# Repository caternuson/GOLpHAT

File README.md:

# GOLpHAT
Eagle PCB files for Raspberry Pi Game Of Life psuedo-HAT interface.

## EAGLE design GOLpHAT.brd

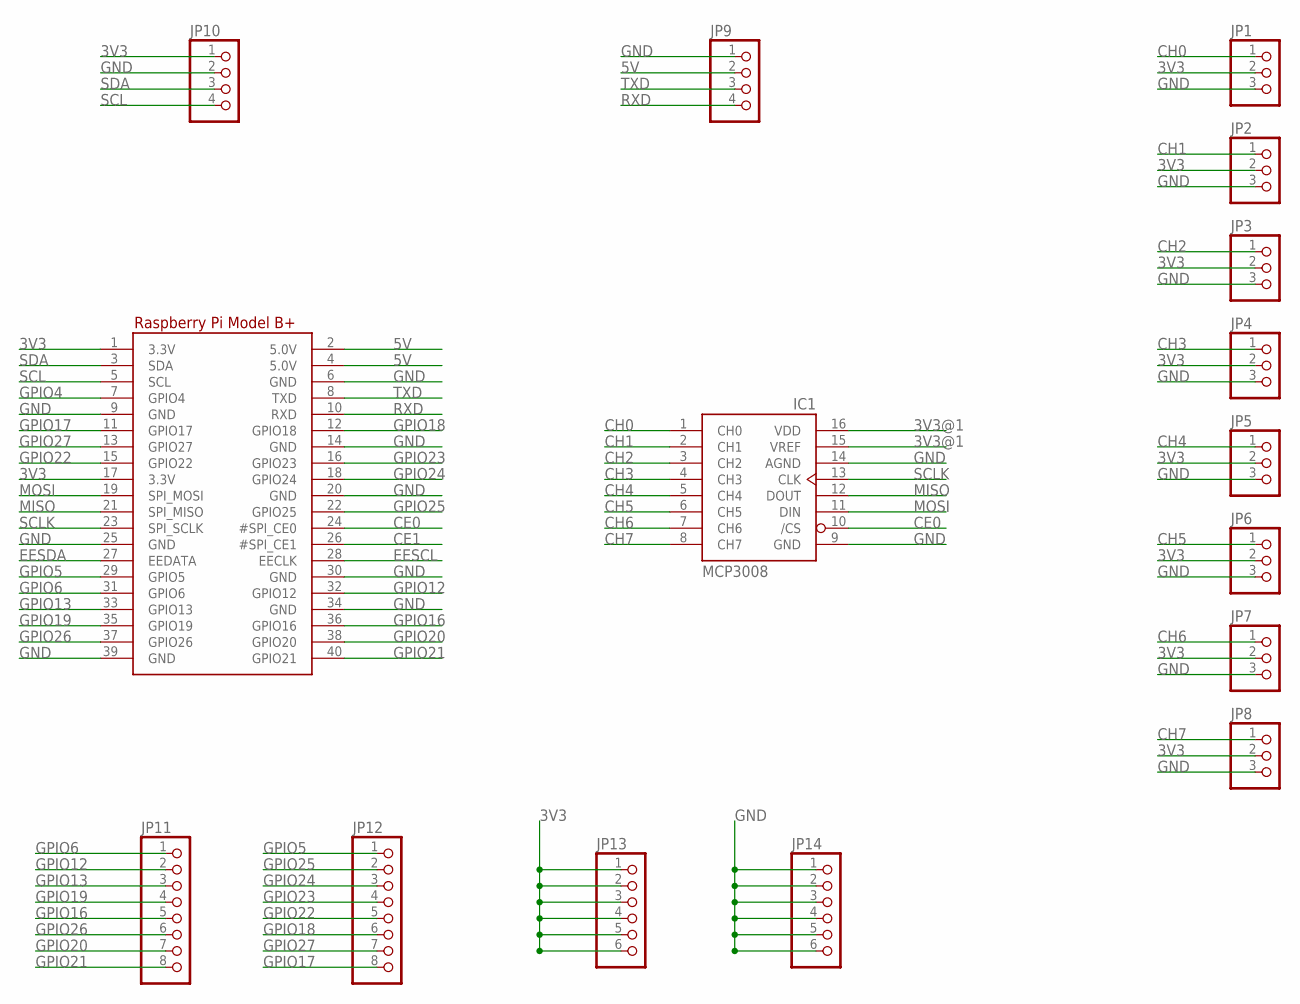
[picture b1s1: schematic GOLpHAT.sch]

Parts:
IC1: MCP3008; DIL16
JP1, JP2, JP3, JP4, JP5, JP6, JP7, JP8: PINHD-1X3; 1X03
JP9, JP10: PINHD-1X4; 1X04
JP11, JP12: PINHD-1X8CLEANBIG; 1X08-CLEANBIG
JP13, JP14: PINHD-1X6CB; 1X06-CLEANBIG
RPI1: RASPBERRYPI_BPLUS_PHAT; PI_BONNET

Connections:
3V3: JP1.2, JP2.2, JP3.2, JP4.2, JP5.2, JP6.2, JP7.2, JP8.2, JP10.1, JP13.1, JP13.2, JP13.3, JP13.4, JP13.5, JP13.6, RPI1.1 (3.3V), RPI1.17 (3.3V)
3V3@1: IC1.15 (VREF), IC1.16 (VDD)
5V: JP9.2, RPI1.2 (5.0V), RPI1.4 (5.0V)
CE0: IC1.10 (/CS), RPI1.24 (#SPI_CE0)
CE1: RPI1.26 (#SPI_CE1)
CH0: IC1.1 (CH0), JP1.1
CH1: IC1.2 (CH1), JP2.1
CH2: IC1.3 (CH2), JP3.1
CH3: IC1.4 (CH3), JP4.1
CH4: IC1.5 (CH4), JP5.1
CH5: IC1.6 (CH5), JP6.1
CH6: IC1.7 (CH6), JP7.1
CH7: IC1.8 (CH7), JP8.1
EESCL: RPI1.28 (EECLK)
EESDA: RPI1.27 (EEDATA)
GND: IC1.9 (GND), IC1.14 (AGND), JP1.3, JP2.3, JP3.3, JP4.3, JP5.3, JP6.3, JP7.3, JP8.3, JP9.1, JP10.2, JP14.1, JP14.2, JP14.3, JP14.4, JP14.5, JP14.6, RPI1.6 (GND), RPI1.9 (GND), RPI1.14 (GND), RPI1.20 (GND), RPI1.25 (GND), RPI1.30 (GND), RPI1.34 (GND), RPI1.39 (GND)
GPIO4: RPI1.7 (GPIO4)
GPIO5: JP12.1, RPI1.29 (GPIO5)
GPIO6: JP11.1, RPI1.31 (GPIO6)
GPIO12: JP11.2, RPI1.32 (GPIO12)
GPIO13: JP11.3, RPI1.33 (GPIO13)
GPIO16: JP11.5, RPI1.36 (GPIO16)
GPIO17: JP12.8, RPI1.11 (GPIO17)
GPIO18: JP12.6, RPI1.12 (GPIO18)
GPIO19: JP11.4, RPI1.35 (GPIO19)
GPIO20: JP11.7, RPI1.38 (GPIO20)
GPIO21: JP11.8, RPI1.40 (GPIO21)
GPIO22: JP12.5, RPI1.15 (GPIO22)
GPIO23: JP12.4, RPI1.16 (GPIO23)
GPIO24: JP12.3, RPI1.18 (GPIO24)
GPIO25: JP12.2, RPI1.22 (GPIO25)
GPIO26: JP11.6, RPI1.37 (GPIO26)
GPIO27: JP12.7, RPI1.13 (GPIO27)
MISO: IC1.12 (DOUT), RPI1.21 (SPI_MISO)
MOSI: IC1.11 (DIN), RPI1.19 (SPI_MOSI)
RXD: JP9.4, RPI1.10 (RXD)
SCL: JP10.4, RPI1.5 (SCL)
SCLK: IC1.13 (CLK), RPI1.23 (SPI_SCLK)
SDA: JP10.3, RPI1.3 (SDA)
TXD: JP9.3, RPI1.8 (TXD)

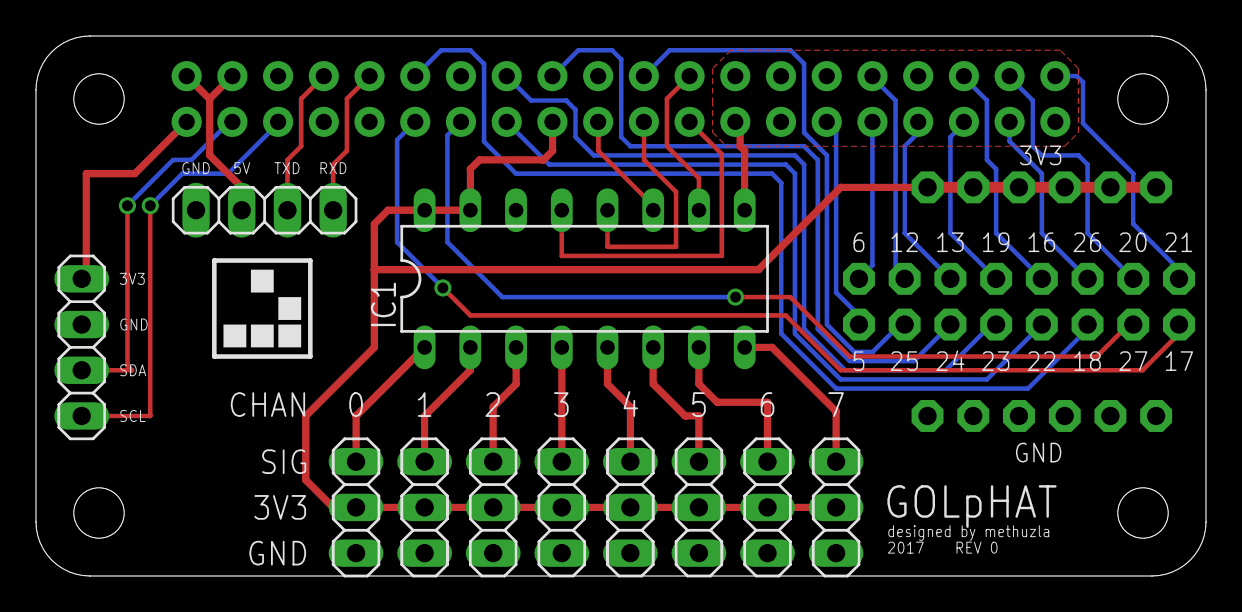
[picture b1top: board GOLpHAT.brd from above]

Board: 2 copper layers, 65.0 x 30.0 mm, 16 parts (0 on the bottom side), 36 nets.

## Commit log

2017-04-19 adding files
